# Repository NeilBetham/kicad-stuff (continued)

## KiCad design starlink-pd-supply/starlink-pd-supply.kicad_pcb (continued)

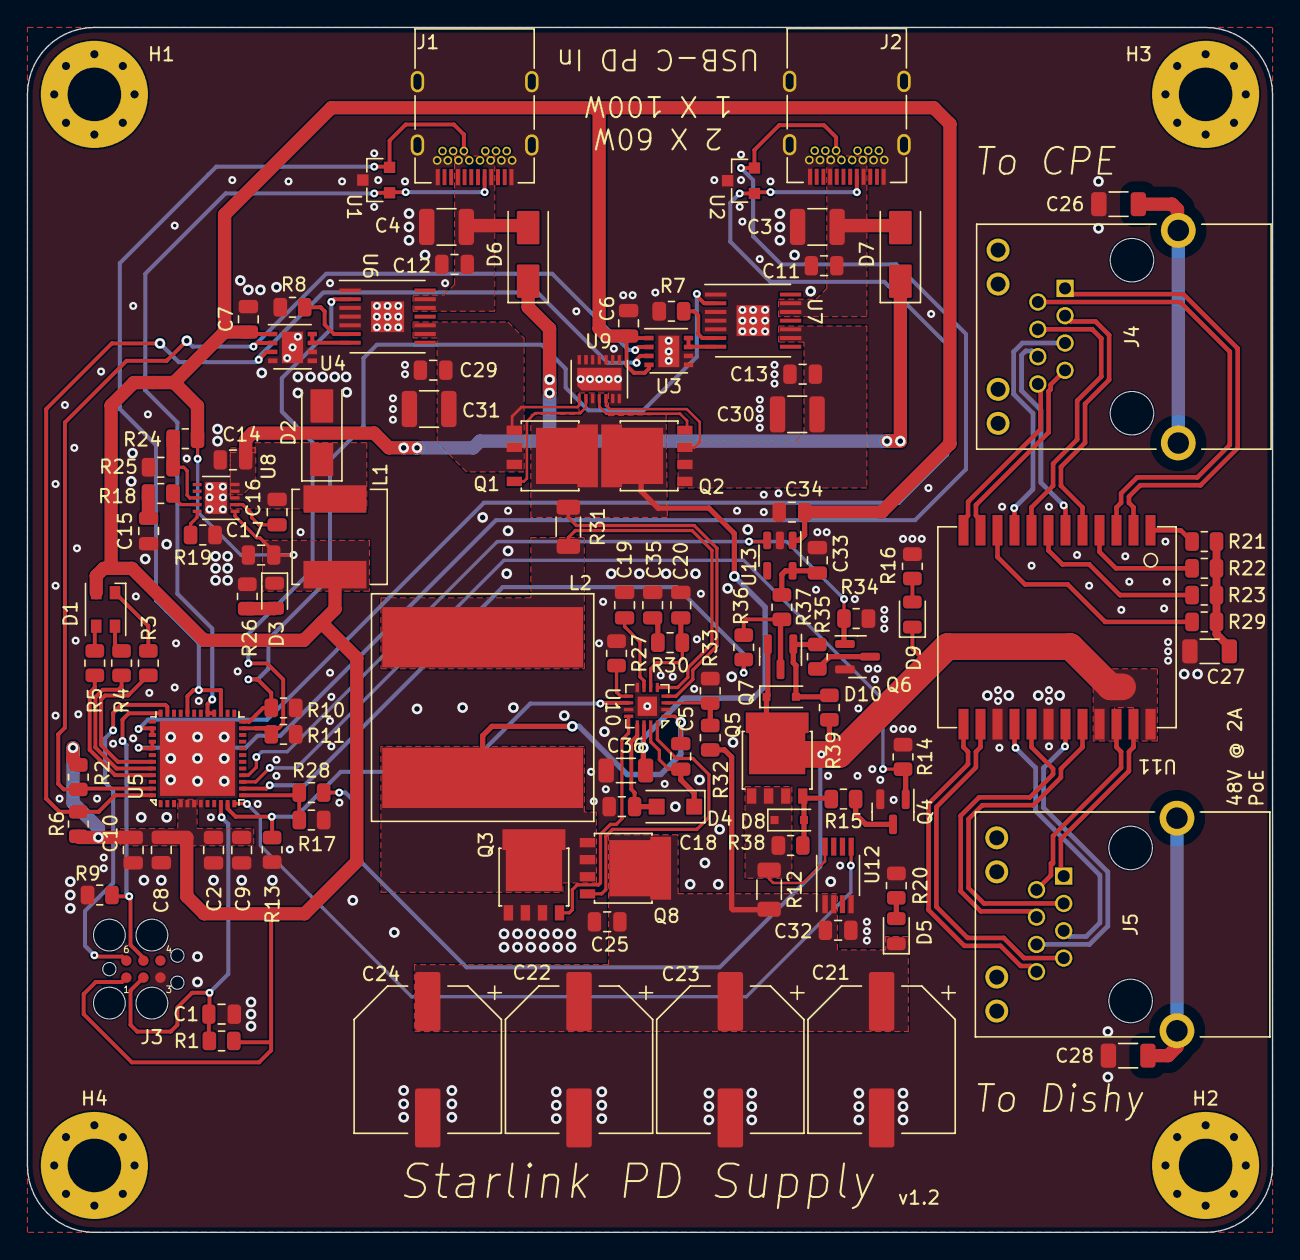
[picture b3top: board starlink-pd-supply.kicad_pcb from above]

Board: 4 copper layers, 93.0 x 90.0 mm, 117 parts (0 on the bottom side), 89 nets.

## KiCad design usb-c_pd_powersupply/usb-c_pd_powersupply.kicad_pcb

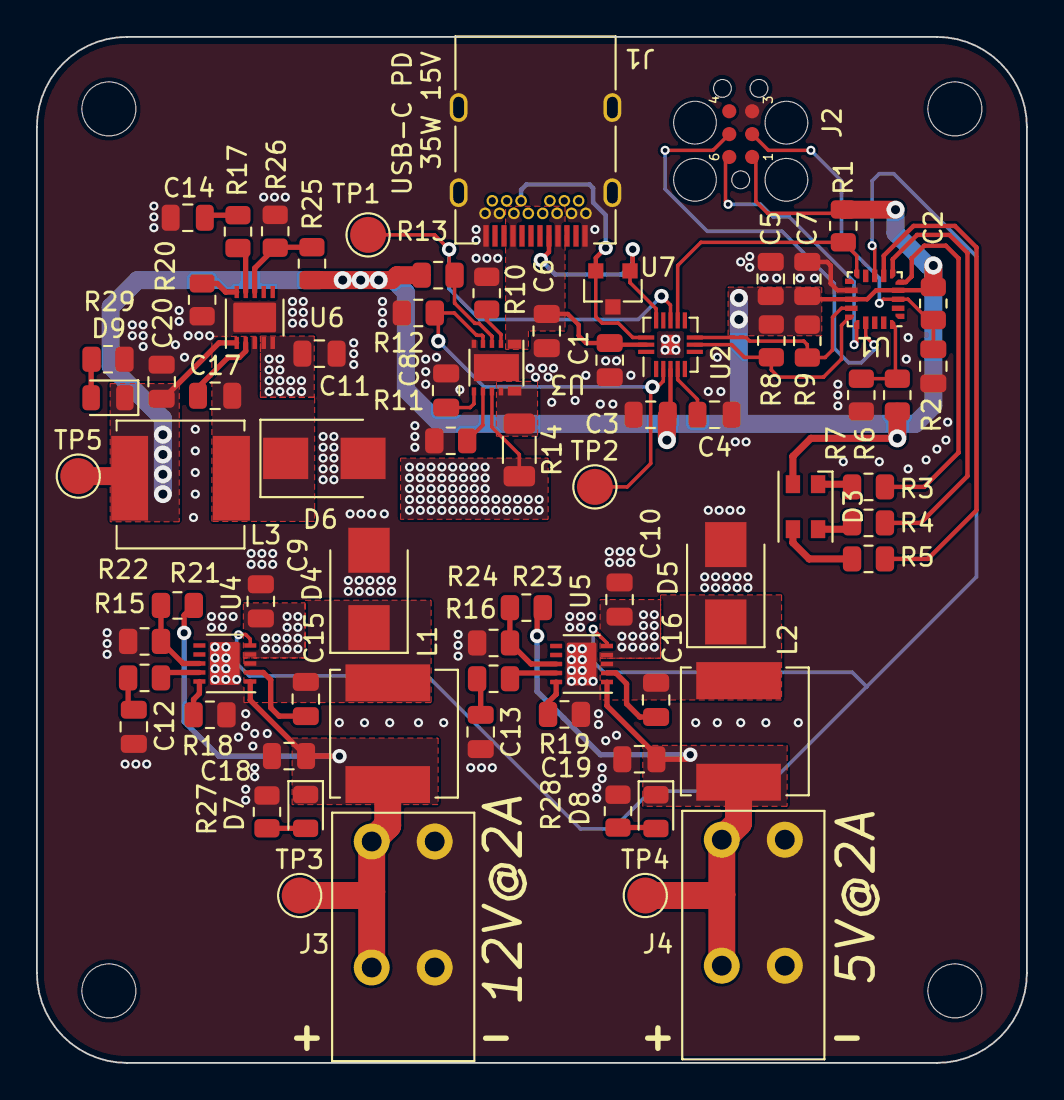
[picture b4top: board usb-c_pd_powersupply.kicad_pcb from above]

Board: 4 copper layers, 55.0 x 57.0 mm, 78 parts (0 on the bottom side), 50 nets.

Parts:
C1, C3, C4: 2.2uF; C_0805_2012Metric
C2, C5: 0.1uF; C_0805_2012Metric
C6, C7, C9: 10uF; C_0805_2012Metric
C8: 0.001uF; C_0805_2012Metric
C10, C11: 4.7uF; C_0805_2012Metric
C12, C13, C14: 470pF; C_0805_2012Metric
C15, C16, C17: 0.47uF; C_0805_2012Metric
C18, C19, C20: 22uF; C_0805_2012Metric
D3: LED_RABG; LED_Cree-PLCC4_3.2x2.8mm_CCW
D4, D5, D6: D_Schottky; D_SMB
D7, D8, D9: LED; LED_0805_2012Metric
J1: USB_C_Receptacle; Wurth_632723300011
J2: TC2030-SWD; TC2030-IDC-FP
J3, J4: Conn_01x02; PhoenixContact_1823638
L1: 10uH; SRP0620
L2, L3: 4.7uH; SRP0620
R1, R2, R7, R8, R9, R12, R13: 10k; R_0805_2012Metric
R3, R4, R5, R29: 500; R_0805_2012Metric
R6: NP; R_0805_2012Metric
R10: 20k; R_0805_2012Metric
R11: 30k; R_0805_2012Metric
R14: 10m; R_1206_3216Metric
R15: 26.1k; R_0805_2012Metric
R16: 16.2k; R_0805_2012Metric
R17: 14k; R_0805_2012Metric
R18, R19, R20: 40.2k; R_0805_2012Metric
R21: 715k; R_0805_2012Metric
R22: 50k; R_0805_2012Metric
R23: 536k; R_0805_2012Metric
R24, R26: 100k; R_0805_2012Metric
R25: 316k; R_0805_2012Metric
R27: 1.5k; R_0805_2012Metric
R28: 1k; R_0805_2012Metric
REF: MountingHole_3mm
REF#2, REF#3: MountingHole_3mm
TP1, TP2, TP3, TP4, TP5: TestPoint; TestPoint_Pad_D2.0mm
U1: STM32L011; UFQFPN-20
U2: PTN5110; HX2QFN16
U3: AOZ1375DI; DFN-12L
U4, U5, U6: LT3685; DFN-10
U7: CDSOT23-0502B; SOT23-3L

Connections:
+3V3: C3.2, C5.1, C7.1, C20.1, D3.2 (A), D9.1 (K), J2.1 (VCC), L3.2, R1.2, R2.2, R6.1, R8.1, R9.1, R13.2, R25.2, TP5.1, U1.4 (VDDA), U1.13 (VDD), U2.3 (VDD), U6.1 (BD)
+5V: C19.1, D8.1 (K), J4.1, L2.2, R23.2, TP4.1, U5.1 (BD)
+12V: C18.1, D7.1 (K), J3.1, L1.2, R21.2, TP3.1, U4.1 (BD)
/3V3_SW: C17.2, D6.1 (K), L3.1, U6.3 (SW)
/5V_SW: C16.2, D5.1 (K), L2.1, U5.3 (SW)
/12V_SW: C15.2, D4.1 (K), L1.1, U4.3 (SW)
/ALERT_N: R1.1, U1.10 (PA7), U2.10 (ALERT_N)
/CC1: J1.A5 (CC1), U2.13 (CC1), U7.1
/CC2: J1.B5 (CC2), U2.14 (CC2), U7.2
/EN_SINK: R12.1, TP2.1, U2.2 (EN_SNK1), U3.5 (EN)
/IND_B: R5.2, U1.7 (PA4)
/IND_G: R4.1, U1.6 (PA1)
/IND_R: R3.1, U1.5 (PA0/CK_IN)
/OUT_EN: U1.8 (PA5), U4.5 (RUN/SS), U5.5 (RUN/SS)
/PD_PHY_SCL: R9.2, U1.14 (PA9), U2.8 (I2C_SCL)
/PD_PHY_SDA: R8.2, U1.15 (PA10), U2.7 (I2C_SDA)
/SWDCLK: J2.5 (SWDCLK), U1.17 (PA14)
/SWDIO: J2.6 (SWDIO), U1.16 (PA13)
/VBUS: C1.2, C6.1, J1.A4 (VBUS), J1.A9 (VBUS), J1.B4 (VBUS), J1.B9 (VBUS), U2.15 (VBUS), U3.1 (VBUS)
/VBUS_FAULT: R13.1, TP1.1, U2.11 (FAULT_N), U3.4 (FLTB)
/VBUS_SW: C9.1, C10.1, C11.1, R14.2, U3.9 (CSP), U4.4 (Vin), U5.4 (Vin), U6.4 (Vin), U6.5 (RUN/SS)
/nRESET: C2.2, J2.2 (nRESET), R2.1, U1.3 (NRST)
GND: C1.1, C2.1, C3.1, C4.2, C5.2, C6.2, C7.2, C8.2, C9.2, C10.2, C11.2, C12.2, C13.2, C14.2, C18.2, C19.2, C20.2, D4.2 (A), D5.2 (A), D6.2 (A), J1.A1 (GND), J1.A12 (GND), J1.B1 (GND), J1.B12 (GND), J1.S1 (SHIELD), J2.3 (GND), J3.2, J4.2, R7.2, R10.1, R11.1, R12.2, R18.1, R19.1, R20.1, R22.2, R24.2, R26.2, R27.1, R28.1, R29.1, U1.12 (VSS), U2.17 (GND), U3.6 (GND), U3.13 (GND), U4.11 (GND), U5.11 (GND), U6.11 (GND), U7.3
unnamed: C4.1, U2.4 (BYPASS)
unnamed: C8.1, U3.7 (SS)
unnamed: C12.1, R15.1
unnamed: C13.1, R16.1
unnamed: C14.1, R17.1
unnamed: C15.1, U4.2 (BOOST)
unnamed: C16.1, U5.2 (BOOST)
unnamed: C17.1, U6.2 (BOOST)
unnamed: D3.1 (RK), R3.2
unnamed: D3.3 (BK), R5.1
unnamed: D3.4 (GK), R4.2
unnamed: D7.2 (A), R27.2
unnamed: D8.2 (A), R28.2
unnamed: D9.2 (A), R29.2
unnamed: R6.2, R7.1, U1.20 (PB9/BOOT0)
unnamed: R10.2, U3.3 (POVP)
unnamed: R11.2, U3.8 (ILIM)
unnamed: R14.1, U3.10 (CSN), U3.11 (VINT)
unnamed: R15.2, U4.9 (Vc)
unnamed: R16.2, U5.9 (Vc)
unnamed: R17.2, U6.9 (Vc)
unnamed: R18.2, U4.10 (Rt)
unnamed: R19.2, U5.10 (Rt)
unnamed: R20.2, U6.10 (Rt)
unnamed: R21.1, R22.1, U4.8 (FB)
unnamed: R23.1, R24.1, U5.8 (FB)
unnamed: R25.1, R26.1, U6.8 (FB)
